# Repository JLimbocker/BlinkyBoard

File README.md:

BlinkyBoard
===========

This repository contains the firmware and design files for the SMU Innovation Gym Blinky Board.

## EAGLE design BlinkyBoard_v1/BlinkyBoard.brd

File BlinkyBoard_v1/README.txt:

=========================================================
Blink

This library was written by Jeff Limbocker, Spring 2014.
Release Version 1.0
=========================================================

Notes:
=========================================================
This library is designed for use with the MSP430g2553 IC. 
Support for other MSP430 MCUs is not guaranteed.

Support for the analog breakout is not yet developed.

To use the library:
=========================================================
Include the library in your Energia Project:

#include "Blink.h"

Declare a Blink object:

Blink blinky;

Tell it to blink:

blinky.set(LED, COLOR);

Details:
=========================================================
Below is a summary of the public functions in the library:

    void set(int LED, int Color)
      This function allows the user to set the LED to one of seven input colors,
        R G B C Y M W, or Off 'O'
      The LED is selected by the number it is labeled by on the PCB.
      
    void chaser(int color)
      This function is a basic chaser pattern.  The color is provided as a parameter.
      
    void strobe(int color)
      This function is a basic strobe pattern.  The color is provided as a parameter.
      
    void SMU()
      This function blinks the LEDs in a diagonal Red/Blue pattern.

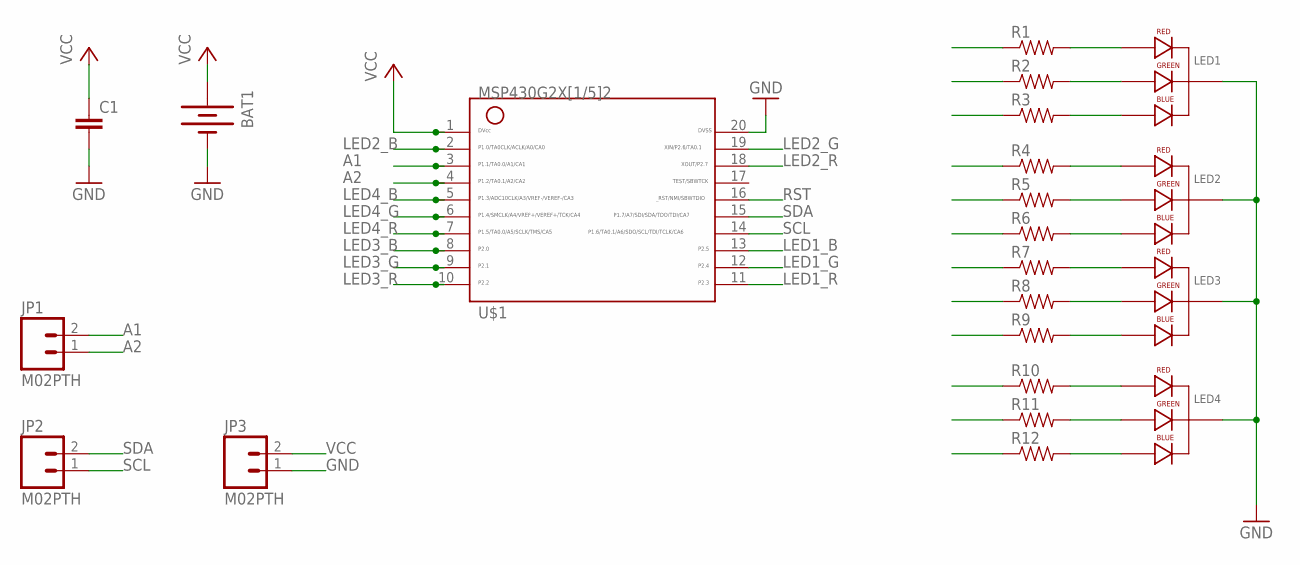
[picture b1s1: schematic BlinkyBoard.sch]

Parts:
BAT1: BATTERY20PTH; BATTCOM_20MM_PTH
C1: CAPKIT; CAP-PTH-SMALL-KIT
JP1, JP2, JP3: M02PTH; 1X02
LED1, LED2, LED3, LED4: LED-RGB-CC-THRUDIFFUSE; LED-RGB-THRU
R1, R2, R3, R4, R5, R6, R7, R8, R9, R10, R11, R12: RESISTORKIT; AXIAL-0.3-KIT
U$1: G2X[1/5]2---N20; N20

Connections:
A1: JP1.2, U$1.3
A2: JP1.1, U$1.4
GND: BAT1.2 (-), C1.2, JP3.1, LED1.2 (CATHODE), LED2.2 (CATHODE), LED3.2 (CATHODE), LED4.2 (CATHODE), U$1.20
LED1_B: R3.P$1 (1), U$1.13
LED1_G: R2.P$1 (1), U$1.12
LED1_R: R1.P$1 (1), U$1.11
LED2_B: R6.P$1 (1), U$1.2
LED2_G: R5.P$1 (1), U$1.19
LED2_R: R4.P$1 (1), U$1.18
LED3_B: R9.P$1 (1), U$1.8
LED3_G: R8.P$1 (1), U$1.9
LED3_R: R7.P$1 (1), U$1.10
LED4_B: R12.P$1 (1), U$1.5
LED4_G: R11.P$1 (1), U$1.6
LED4_R: R10.P$1 (1), U$1.7
unnamed: LED1.1 (RED_CATHODE), R1.P$2 (2)
unnamed: LED1.3 (GREEN_CATHODE), R2.P$2 (2)
unnamed: LED1.4 (BLUE_CATHODE), R3.P$2 (2)
unnamed: LED2.1 (RED_CATHODE), R4.P$2 (2)
unnamed: LED2.3 (GREEN_CATHODE), R5.P$2 (2)
unnamed: LED2.4 (BLUE_CATHODE), R6.P$2 (2)
unnamed: LED3.1 (RED_CATHODE), R7.P$2 (2)
unnamed: LED3.3 (GREEN_CATHODE), R8.P$2 (2)
unnamed: LED3.4 (BLUE_CATHODE), R9.P$2 (2)
unnamed: LED4.1 (RED_CATHODE), R10.P$2 (2)
unnamed: LED4.3 (GREEN_CATHODE), R11.P$2 (2)
unnamed: LED4.4 (BLUE_CATHODE), R12.P$2 (2)
RST: U$1.16
SCL: JP2.1, U$1.14
SDA: JP2.2, U$1.15
VCC: BAT1.1 (+), C1.1, JP3.2, U$1.1

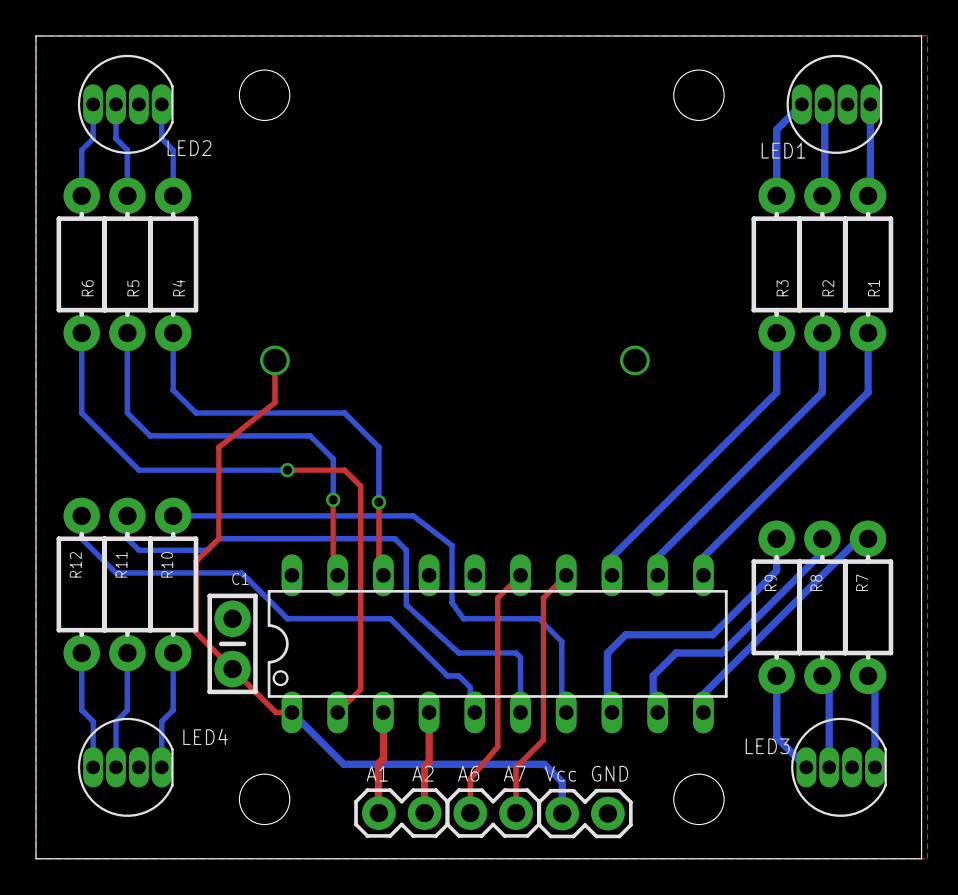
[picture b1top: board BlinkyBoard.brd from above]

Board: 2 copper layers, 49.2 x 45.7 mm, 22 parts (1 on the bottom side), 30 nets.

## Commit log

2014-08-22 First Commit of board files
2014-08-22 Updated Directory Structure

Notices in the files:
parts and their libraries:
SparkFun-Capacitors: Licensing: CC v3.0 Share-Alike You are welcome to use this library for commercial purposes.
